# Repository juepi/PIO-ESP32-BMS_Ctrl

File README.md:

# Introduction 
This project is intended to be used as an WiFi/MQTT interface to the [Daly Smart BMS Systems](https://www.aliexpress.com/store/4165007) and Victron VE.Direct devices based on my PlatformIO ESP32 Template.  
Primarily, the code reads status data from the Daly BMS, Victron VE.Direct PV charger and SmartShunt and sends it to your MQTT broker at a configurable interval. It automatically switches the load-SSR on if the batteries are fully charged (2 configurable SOC limits) and off if the batteries are drained (also configureable SOC limit). Load-SSR can also be switched manually by setting the corresponding MQTT topic to `on` or `off`. The primary source for the battery SOC is the **Victron SmartShunt**.  
Last but not least, the firmware also allows you to handle an external active balancer through an additional SSR as recommended by [Andy](https://www.youtube.com/watch?v=yPmwrPOwC3g). However, i have added a second condition beside the 3.4V cell voltage: we're only enabling the active balancer if the voltage difference between the highest and lowest cell is above an configurable threshold (defaults to 30mV, configurable via MQTT topic `t_Ctrl_Cfg_SSR2_CdiffOn`).  
To configure the firmware for your needs, see files `user-config.h` and `mqtt-ota-config.h`, also see [**PlatformIO ESP32 Template**](https://github.com/juepi/PIO-ESP32-Template) readme (WiFi setup etc.).

## Mandatory Hardware Requirements
- 1x [WEMOS S2 Mini](https://www.wemos.cc/en/latest/s2/s2_mini.html) or any other ESP32 should work (adopt `platformio.ini`to your needs)
- 1x [Daly Smart BMS Systems](https://www.aliexpress.com/store/4165007) with UART port
- a Lithium battery fitting your requirements and BMS
- 1x [Victron SmartSolar](https://www.victronenergy.com/solar-charge-controllers/smartsolar-100-30-100-50) charger (or any other charger supporting the text version of the VE.Direct protocol)
- 1x [Victron SmartShunt](https://www.victronenergy.com/battery-monitors/smart-battery-shunt) with the amps required for your setup
- 3x [ADUM1201 UART Isolators](https://www.amazon.de/s?k=adum1201) or any other digital isolators you prefer
- 1x [AQW212EH Optocoupler](https://na.industrial.panasonic.com/products/relays-contactors/semiconductor-relays/lineup/photomos-relays/series/12512/model/12513)
- 1x [Active Balancer](https://aliexpress.com/item/4001176521939.html)
- a local WiFi network with a MQTT broker
- Sunlight. :wink:

## Status
What you are looking at here is the **second major release** of this firmware. If you want to see how it all started or you're interested in the problems I've encountered up to this point, take a look at the [final v1 release readme](https://github.com/juepi/PIO-ESP32-BMS_Ctrl/tree/v1.3.0).  
The hardware part is also finished now, see [KiCad folder](https://github.com/juepi/PIO-ESP32-BMS_Ctrl/tree/main/KiCad).

## Safety Guide
Keep in mind that you are working with potentially dangerous electricity levels depending on the hardware you use. Take any precautions necessary!

## Local Requirements
You need to do the initial battery setup on the Daly BMS using the included Bluetooth adapter and Daly's SmartBMS app, as the used [library](https://github.com/maland16/daly-bms-uart) does not support setting configuration parameters. Victron devices can use the VictronConnect App in parallel to the (read only) serial output on the VE.Direct port.  
An active balancer is highly recommended, as the internal passive balancer of the Daly BMS is useless. [Andy from the Off-Grid Garage](https://www.youtube.com/watch?v=yPmwrPOwC3g) has picked up this topic recently, and i've decided to add the active-balancing control as he suggests it into the firmware. Note that you will need an active balancer that will allow you to start the balancing by shorting 2 pins, like [this one from AliExpress](https://aliexpress.com/item/4001176521939.html). You will need to remove the solder chunk from the pads labeled "Run", this will reveal 2 seperate soldering pads. Solder 2 wires to the pads and connect them to an optocoupler output, in example [AQW212EH](https://na.industrial.panasonic.com/products/relays-contactors/semiconductor-relays/lineup/photomos-relays/series/12512/model/12513).

## An important notice on connecting the ESP32 to your BMS and VE.Direct
Take caution when connecting the ESP to the UART ports: the internal electronics of the BMS (including UART port) use "battery ground", whereas other connected devices (i.e. load, charger) use the "power ground". **NEVER EVER** connect these different grounds or magic smoke will leave your electronics! To avoid this, make sure to isolate **anything** coming from or going into the UART ports of the Daly BMS and your VE.Direct devices. For UART RX/TX, a **ADUM1201** isolator chip works well for me.

## Credits
Thanks to [maland16 and softwarecrash](https://github.com/maland16/daly-bms-uart) for providing a library to interact with the Daly Smart BMS.  
Thanks to [cterwilliger](https://github.com/cterwilliger/VeDirectFrameHandler/tree/master) for his Victron VE.Direct frame handler, which has been integrated into this project since v1.2.0. Note that the source is in the lib directory, not from github, as i needed to include [the buffer overflow patch](https://github.com/cterwilliger/VeDirectFrameHandler/pull/10). I have also added a frameCounter which increments when a valid frame is decoded (to ease handling of fresh data) and a function which looks up array index numbers by Name label (required for SmartShunt!).

# Bugs and Workarounds
- Both data frame arrays of the VeDirectFrameHandler (Charger and SmartShunt) keep increasing over time due to transmission/decoding errors (I assume!) leading to new (non-existing) data labels/values that are added to the arrays. VeDirectFrameHandler maxes out at 40 Labels, so this should not lead to any problems (in terms of buffer overflow), not sure how this is possible however as every frame has a checksum. Due to this problem, also garbage values will be decoded every now and then, so I've added additional validity checks when new data was received (especially SoC).
- VeDirectFrameHandler data from the SmartShunt is "sorted" randomly in the veValue/veName arrays, which breaks the "hardcoded" index numbers I used to get the values from the data arrays. I've fixed this by adding a function to the library that allows you to fetch the arrays index number from a given veName tag. This may also happen with data from the SmartSolar chargers (one out of 2 chargers show this "problem" in my setup).
- OneWire doesn't seem to work on high-numbered GPIO pins (tested with > 36); using IO4 works fine!
- It seems that a high frequency toggling of SSR1 and SSR3 relay may occured at firmware boot - i have not been able to identify the root cause, it only happens when the SSRs automatic-mode is enabled. Done some obviously not so successful improvements over time, but as of **v2.6.1** this error still seems to occur randomly. My latest idea on how to work around this issue was to delay handling of the "auto" SSR settings for 15sec after firmware boot with **v2.7.0**. Time will tell if this helped, first tests look promising.
- An **"offgrid mode"** has been added (**v2.4.3**) as i've experienced that certain battery loads (like my offgrid inverter) causes the OneWire communication to fail. I assume that the inverter causes high noise on the DC wires, but as only OneWire communication is affected, i decided to add this MQTT on/off switchable function to allow skipping OneWire readouts (all sensors will be set to 11°C in offgrid mode, see `t_Ctrl_Cfg_Offgrid_Mode` in `user-config.h`). Plugging in the offgrid inverter is only done in case of a long lasting power outage, which has not happened yet (and hopefully never will), so i can live with that limitation. **A note on failing OneWire communication:** in my case the only way to recover OW-communication was to power down the ESP (remove power from the OW sensors), it seems that the controller inside the sensors hung and rebooting the ESP did not help.
- Although all serial communication to the BMS and Victron devices uses some sort of CRC, it rarely happens that implausible values are reported. To avoid reacting with failsafe actions due to wrong values, several plausibility checks have been added starting with `v2.0.2`.

# Version History

## v2.0.0
- Initial Commit, removed overhead from v1
- Improved handling of SSRs (manual switching through MQTT)

## v2.0.1
- Added condition to enable balancer on large cell voltage diff
- Removed condition to enable balancer on PV power threshold
- removed balancer "minimum ON duration" timer
- cleaned up serial connection state handling
- added more textual output to `CtrlStatTXT` topic; now publishes info on every action the controller takes (like enable/disable load or balancer)

## v2.0.2
- MQTT topic `Daly_dV` now reports mV
- Sending int instead of float  to MQTT topics for Daly temperature and SOC
- Added error detection for VE.Direct data readouts (SOC)
- Added some currently unused pin defines to match KiCad schematics
- Added additional plausibility check for SoC data from SmartShunt

## v2.0.3
- Added optional OneWire support for DS18B20 temperature sensors (enable in `platformio.ini`) - doesn't work yet

## v2.0.4
- Moved OneWire GPIO to IO4, this one works

## v2.1.0
- Fixed missing VeDirectFrameHandler lib (**see Note below!**), which i've trashed somehow as it seems..; now loaded through `platformio.ini`
- Fixed Hostname limitation of ESP32-Template
- Renamed `user_setup.h` to more suitable `user-config.h`

## v2.1.1
- Added SSR3 and SSR4 initialization (default state OFF)
- Fixed high delays due to OneWire `getTempCByIndex()` calls when no sensors are available
- Added Timeout handling for OneWire sensors
- Improved VE.Direct data error and connection handling
- Bugfix for WiFi hostname setup (compile error for v2.1.0 when using hostname with dash)
- Added SSR3 for manual switching through MQTT
- Added safety shutdown of loads when communication to Daly BMS or Victron SmartShunt runs into timeout

## v2.2.0
- Reworked Load and Balancer SSR handling (now fully configurable through MQTT topics)
- Updated MQTT subscription handling (PIO-ESP32-Template v1.1.0)
- OTA Updates are now mandatory
- Removed MQTT control of Daly BMS FETs (they are a safety feature, you shouldn't mess with them manually)
- Added additional safety features (Balancer alarm mode for high cellDiff, load shutdown for minimum battery voltage)

## v2.2.1
- Re-added periodic publishing of SSR states (basically for plots in FHEM)
- Bugfix on SSR state handling at firmware boot

## v2.3.0
- Added ability to run without WiFi / MQTT broker connection (based on [**PIO-ESP32-Template v1.2.0**](https://github.com/juepi/PIO-ESP32-Template))

## v2.3.1
- Removed unneccesary SSR handling at firmware boot (just let auto-mode do the magic)
- Setting all SSR state topics to "OFF" on the broker at startup to match the actual firmware boot state 
- High frequency toggling of SSR3 state at firmware boot hopefully fixed

## v2.4.0
- Added error/recovery handling for over-temperature situations (OW-sensors and Daly BMS sensor)
- Improved under-voltage and communication error/recovery handling
- Removed Balancer Alarm mode, as balancing an empty battery does not make sense
- Added additional safety check to turn off loads at high cell diff voltage (stopping discharge should probably not further increase cell diff)
- Added verification of Daly celldiff readout (reports implausible high changes between 2 readouts in rare occurences)

## v2.4.1
- Minor status output changes (investigating readout error loop on SmartShunt)
- Added ESP reboot when reaching configurable threshold of subsequent SmartShunt read failures (defaults to 60 -> 1 minute)

## v2.4.2
- No longer send Controller status text messages retained
- Added global controller Alarm flag being published via MQTT; if a safety function triggers a critical condition, the flag switches to "on" (see topic `t_Ctrl_Alarm` in `user-config.h`)
- "Bugfix" in SmartShunt SOC verification ("error loop" from v2.4.1 - basically `VSS_MAX_SOC_DIFF` was set too low to 0.5% instead of 5%)

## v2.4.3
- Added status text message when not discarding unrealistic high Daly BMS voltage diff
- Increased max number of unrealistic subsequent voltage diff values from Daly BMS which will be discarded (from 2 to 4)
- Switched balancer power-off condition from single cell to all cells below `SSR2.CVOff` (previous conditions could lead to Auto-mode rapidly toggling balancer if a single cell is above enable and another one is below disable voltage)
- Added "offgrid mode", can be enabled when "noisy" battery loads break OneWire communication (in example, when connecting an offgrid inverter)

## v2.4.4
- Allow larger SOC changes when charger switches to absorption mode (battery full -> SmartShunt corrects SOC to 100%)

## v2.5.0
- Functionality cleanups
    - Removed Low-PPV threshold (everything below High-PPV threshold is considered as low now)
    - Removed Low/High-PPV Off-SOC for SSRs (simply useless - switched to a single Off-SOC)
- Removed ESP reboot for SmartShunt read failures (useless)

## v2.5.1
- Use Victron SmartShunt voltage (instead of Daly data) as battery pack voltage source for safety checks
- recover previous SSR Auto-mode settings instead of enabling all auto modes when recovering from critical states

## v2.6.0
- Added support for optional 2nd SmartSolar charger (VE.Direct, using GPIO39 for RX; enable in `platformio.ini`)
- Upgraded to latest `EspSoftwareSerial` library version
- Added plausibility check for SmartShunt pack voltage (discard value if difference to previous readout is more than `VSS_MAX_V_DIFF` defined in `user-config.h`)

## v2.6.1
- Immediately publish Controller-Alarm flag via MQTT when alarm occurs (or recovers)
- Fixed error in cell temperature alarm handling

## v2.7.0
- Added web interface (network status checking / reboot ESP)
- Upgraded underlying [**PIO-ESP32-Template to v1.4.0**](https://github.com/juepi/PIO-ESP32-Template)
- Checking validity of most important Victron SmartShunt data 10sec after firmare startup (ESP will reboot if no valid SOC or voltage is available)
- Automatic SSR-handling is started 15sec after ESP boot if enabled (hopefully solves fast-toggling SSR issue)
- Publishing of data to MQTT will start after `DATA_UPDATE_INTERVAL` to avoid publishing wrong/incomplete data directly at firmware boot

## v2.7.1
- Added Moving Average class to calculate short (1 min) and long (1hr) averages for Victron chargers PPV values
- Added validation of OneWire temperature readouts (reject reading if diff between subsequent readouts is higher than `OW_MAX_TEMP_DIFF`)
- Updated DallasTemperature library to [version 4.0.5](https://registry.platformio.org/libraries/milesburton/DallasTemperature)

# NOTE on missing VeDirectFrameHandler library

I somehow managed to not to include the VeDirectFrameHandler library into previous commits as it was intended. **This affects all versions prior v2.1.0!**  
If you want to build an older release, you can easily fix this by adding my [fork of VeDirectFrameHandler](https://github.com/juepi/VeDirectFrameHandler) into the library section of `platformio.ini`:

```
lib_deps =
    https://github.com/juepi/VeDirectFrameHandler
    ...
```

Have fun,  
Juergen

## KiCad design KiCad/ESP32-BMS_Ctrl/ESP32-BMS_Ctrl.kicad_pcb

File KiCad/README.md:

# KiCad Project Files
The hardware part of the BMS-Controller constists of 2 boards, where the small and simple DE-9 Adaptor board is meant to be placed in your battery box. It will only concentrate all required wires on a 9pin D-Sub connector, allowing you to use a common (straight) serial cable to connect to the actual BMS-Controller board with the ESP32 (which is located outside of the metal battery box in my case).  
Schematics should be straight forward and documented. Don't forget to add isolators into the wires to/from VE.Direct devices and your Daly BMS (i have soldered them directly into the wires, so they are not on the PCBs). Both PCBs only use THT parts (no SMT).

## Optional Features
I have added a second AQW212EH opto-coupler as well as 2 additional dual P-channel MOSFET driven power outputs. This hardware is optional. Depending on your load currents, you may install the paralleled MOSFETs (Q4-Q6) or not. I have done load tests with 2 paralleled MOSFETs with up to 15A without any problems. Do note that you will probably have to install more powerful MOSFETs with lower RDSon than the one mentioned in the schematics for such high currents. I have tested with 2 [IXYS IXTP140P05T](https://www.littelfuse.com/media?resourcetype=datasheets&itemid=309f84bc-aa60-4d40-b2f9-2c59ecb0b7b8&filename=littelfuse-discrete-mosfets-p-channel-ixt-140p05t-datasheet). Additionally, you may want to screw at least small heat sinks to the FETs at this current levels.  
Additionally, i have prepared a pin header connector on the DE-9 adaptor board which will let you connect up to 5 [DS18B20](https://www.analog.com/media/en/technical-documentation/data-sheets/ds18b20.pdf) OneWire temperature sensors in parasitic mode.  
J4 and J5 can be used if you have an "external use" for the OptoMOS outputs of U2. Be sure not to place any other components on the OptoMOS output if you want to use the "external connector" (for J4 -> do not populate R2, R6 and R7, and of course Q2 and Q5) to keep them potential free.

## Production Files
Gerber files are prepared for PCB manufacturing at [jlcpcb.com](https://jlcpcb.com). If you are expecting higher currents on the power outputs, you may want to double up the **copper weight to 2oz** for the BMS-Controller PCB on your order.

# Version History

## v1.1
- Initial commit with some improvements to allow more current on BMS-Controller board (SSR1, SSR3 and SSR4)

## v1.2
- Replaced B2B-XH connector footprints with version w/o guidance hole
- maximized spacing between 2 paralleled MOSFETs to allow mounting a TO-220 heat sink
- Fixed too narrow GND connections for screw terminals; updated Gerber data
- Added silkscreen text to explain installation direction of ESP module

## v1.3
- Re-routed OneWire pin to GPIO4 (tested ok with 2 sensors)

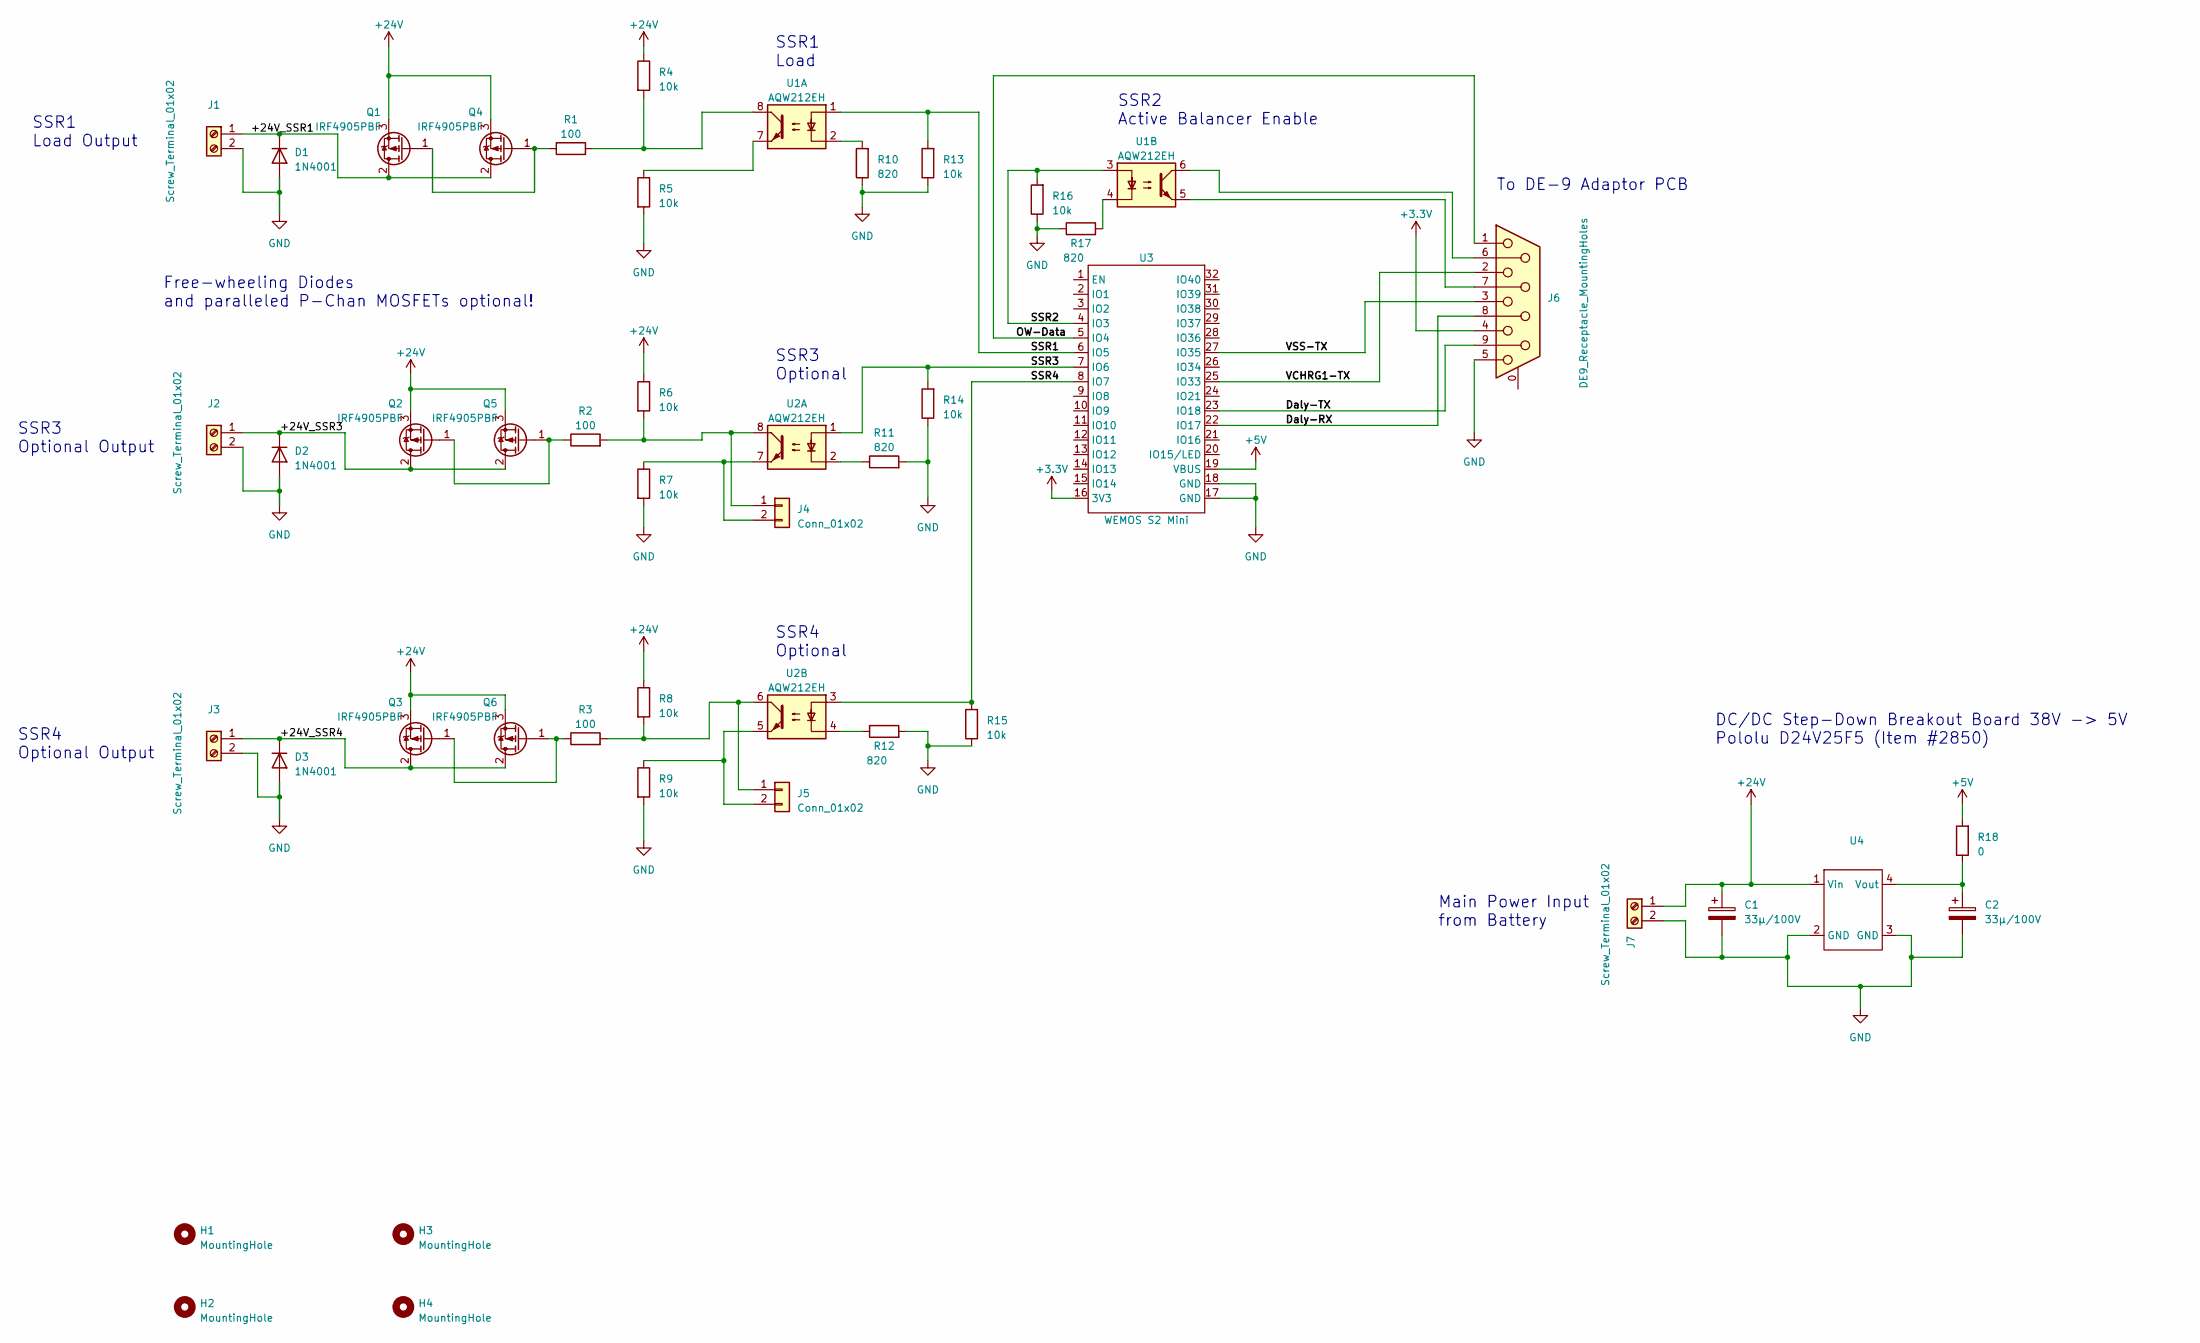
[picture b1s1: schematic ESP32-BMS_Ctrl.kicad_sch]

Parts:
C1, C2: 33µ/100V; CP_Radial_D10.0mm_P5.00mm
D1, D2, D3: 1N4001; D_DO-41_SOD81_P10.16mm_Horizontal
H1, H2, H3, H4: MountingHole; MountingHole_3.2mm_M3
J1, J2, J3, J7: Screw_Terminal_01x02; TerminalBlock_1x02_P5.00mm_Horizontal
J4, J5: Conn_01x02; JST_XH_B2B-XH-A_1x02_P2.50mm_Vertical
J6: DE9_Receptacle_MountingHoles; DSUB-9_Female_Horizontal_P2.77x2.84mm_EdgePinOffset9.90mm_H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
Q1, Q2, Q3, Q4, Q5, Q6: IRF4905PBF; TO-220-3_Vertical
R1, R2, R3: 100; R_Axial_DIN0207_L6.3mm_D2.5mm_P10.16mm_Horizontal
R4, R5, R6, R7, R8, R9, R13, R14, R15, R16: 10k; R_Axial_DIN0207_L6.3mm_D2.5mm_P10.16mm_Horizontal
R10, R11, R12, R17: 820; R_Axial_DIN0207_L6.3mm_D2.5mm_P10.16mm_Horizontal
R18: 0; R_Axial_DIN0207_L6.3mm_D2.5mm_P10.16mm_Horizontal
U1, U2: AQW212EH; DIP-8_W7.62mm_Socket
U3: WEMOS S2 Mini; WEMOS_S2_Mini
U4: Pololu_D24V25F5

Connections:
+3.3V: J6.4, U3.16 (3V3)
+5V: R18.2, U3.19 (VBUS)
+24V: C1.1, J7.1, Q1.3 (S), Q2.3 (S), Q3.3 (S), Q4.3 (S), Q5.3 (S), Q6.3 (S), R4.1, R6.1, R8.1, U4.1 (Vin)
/+24V_SSR1: D1.1 (K), J1.1, Q1.2 (D), Q4.2 (D)
/+24V_SSR3: D2.1 (K), J2.1, Q2.2 (D), Q5.2 (D)
/+24V_SSR4: D3.1 (K), J3.1, Q3.2 (D), Q6.2 (D)
/Daly-RX: J6.8, U3.22 (IO17)
/Daly-TX: J6.9, U3.23 (IO18)
/OW-Data: J6.1, U3.5 (IO4)
/SSR1: R13.2, U1.1, U3.6 (IO5)
/SSR2: R16.2, U1.3, U3.4 (IO3)
/SSR3: R14.2, U2.1, U3.7 (IO6)
/SSR4: R15.2, U2.3, U3.8 (IO7)
/VCHRG1-TX: J6.2, U3.25 (IO33)
/VSS-TX: J6.3, U3.27 (IO35)
GND: C1.2, C2.2, D1.2 (A), D2.2 (A), D3.2 (A), J1.2, J2.2, J3.2, J6.5, J7.2, R5.2, R7.2, R9.2, R10.1, R11.2, R12.2, R13.1, R14.1, R15.1, R16.1, R17.1, U3.17 (GND), U3.18 (GND), U4.2 (GND), U4.3 (GND)
unnamed: J4.1, R2.2, R6.2, U2.8
unnamed: J4.2, R7.1, U2.7
unnamed: J5.1, R3.2, R8.2, U2.6
unnamed: J5.2, R9.1, U2.5
unnamed: J6.6, U1.6
unnamed: J6.7, U1.5
unnamed: Q1.1 (G), Q4.1 (G), R1.1
unnamed: Q2.1 (G), Q5.1 (G), R2.1
unnamed: Q3.1 (G), Q6.1 (G), R3.1
unnamed: R1.2, R4.2, U1.8
unnamed: R5.1, U1.7
unnamed: R10.2, U1.2
unnamed: R11.1, U2.2
unnamed: R12.1, U2.4
unnamed: R17.2, U1.4
unnamed: C2.1, R18.1, U4.4 (Vout)

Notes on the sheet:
To DE-9 Adaptor PCB
Main Power Input from Battery
SSR4 Optional Output
Free-wheeling Diodes and paralleled P-Chan MOSFETs optional!
SSR2 Active Balancer Enable
SSR4 Optional
SSR3 Optional
DC/DC Step-Down Breakout Board 38V -> 5V Pololu D24V25F5 (Item #2850)
SSR1 Load
SSR1 Load Output
SSR3 Optional Output

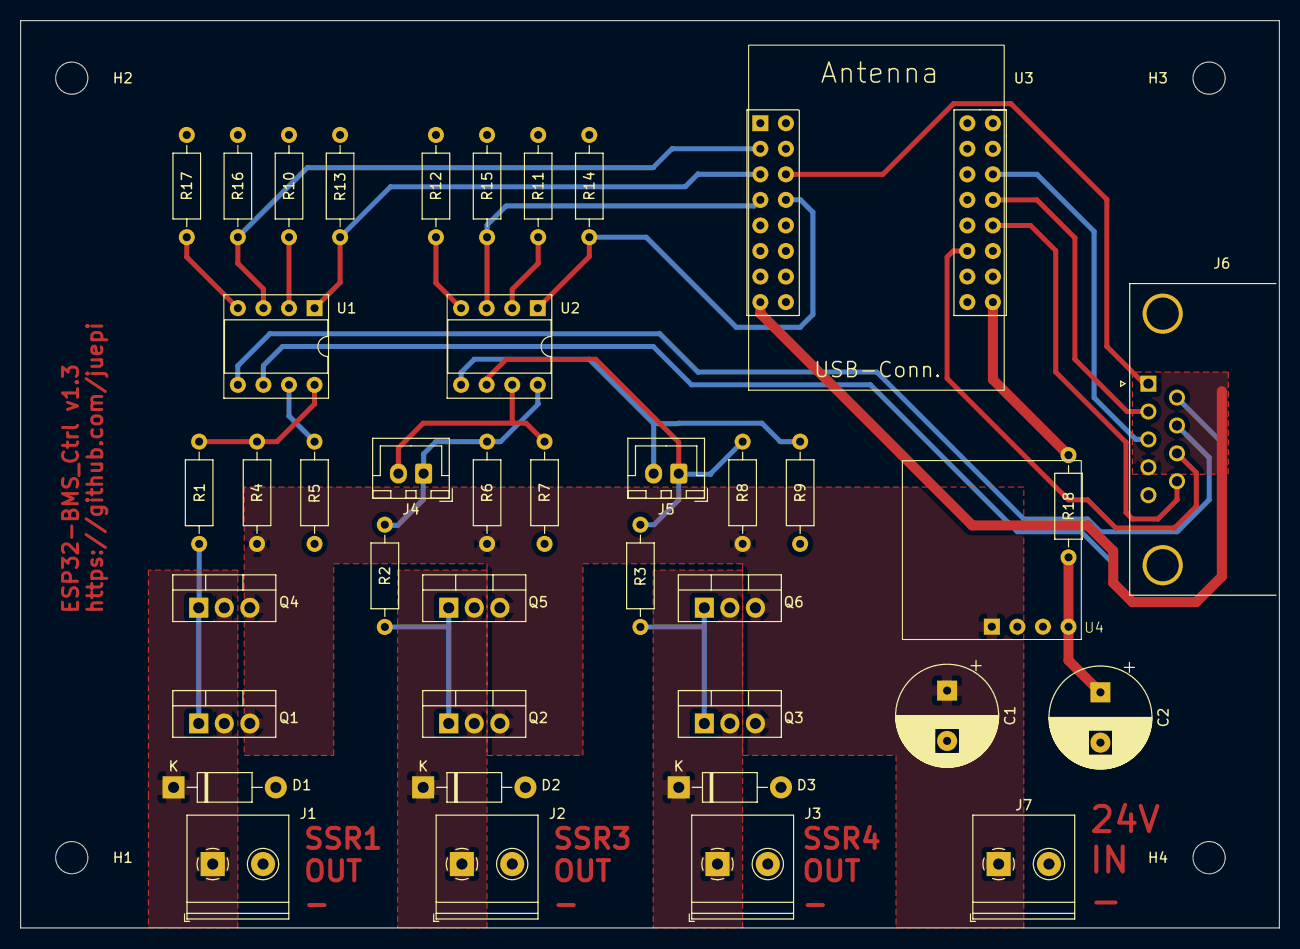
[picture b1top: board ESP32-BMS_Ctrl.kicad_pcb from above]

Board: 2 copper layers, 125.1 x 90.2 mm, 44 parts (0 on the bottom side), 32 nets.

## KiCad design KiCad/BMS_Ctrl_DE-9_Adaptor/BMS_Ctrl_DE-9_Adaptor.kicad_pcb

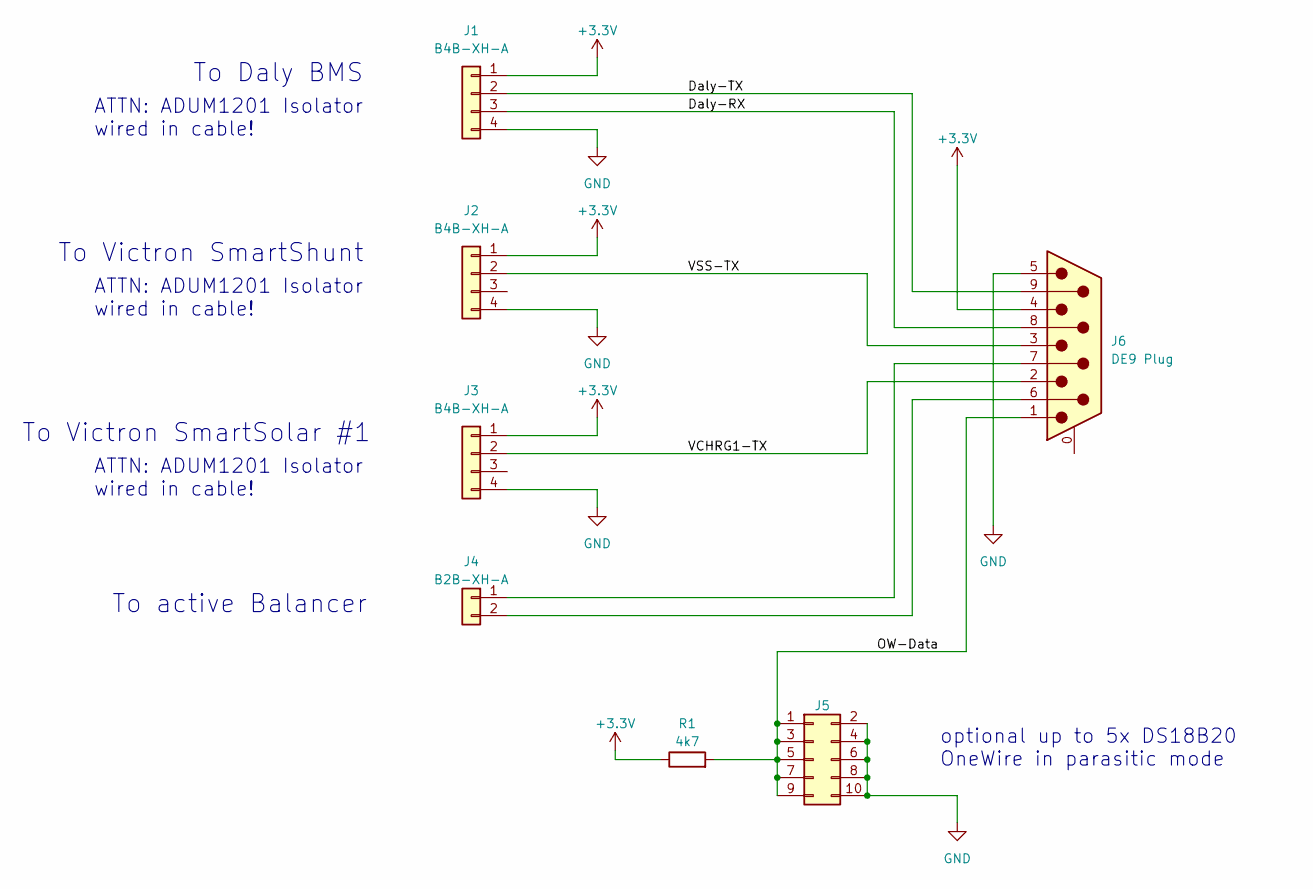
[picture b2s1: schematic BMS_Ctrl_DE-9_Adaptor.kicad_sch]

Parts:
J1, J2, J3: B4B-XH-A; JST_XH_B4B-XH-A_1x04_P2.50mm_Vertical; Manufacturer_Part_Number B4B-XH-A(LF)(SN)
J4: B2B-XH-A; JST_XH_B2B-XH-A_1x02_P2.50mm_Vertical; Manufacturer_PN B2B-XH-A(LF)(SN)
J5: Conn_02x05_Counter_Clockwise; PinHeader_2x05_P2.54mm_Vertical
J6: DE9 Plug; DSUB-9_Male_Horizontal_P2.77x2.84mm_EdgePinOffset9.90mm_Hou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
R1: 4k7; R_Axial_DIN0207_L6.3mm_D2.5mm_P10.16mm_Horizontal

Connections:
+3.3V: J1.1, J2.1, J3.1, J6.4, R1.1
/Daly-RX: J1.3, J6.8
/Daly-TX: J1.2, J6.9
/OW-Data: J5.1, J5.3, J5.5, J5.7, J5.9, J6.1, R1.2
/VCHRG1-TX: J3.2, J6.2
/VSS-TX: J2.2, J6.3
GND: J1.4, J2.4, J3.4, J5.2, J5.4, J5.6, J5.8, J5.10, J6.5
unnamed: J4.1, J6.7
unnamed: J4.2, J6.6

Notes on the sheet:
To Victron SmartSolar #1
ATTN: ADUM1201 Isolator wired in cable!
To Daly BMS
To active Balancer
To Victron SmartShunt
optional up to 5x DS18B20 OneWire in parasitic mode

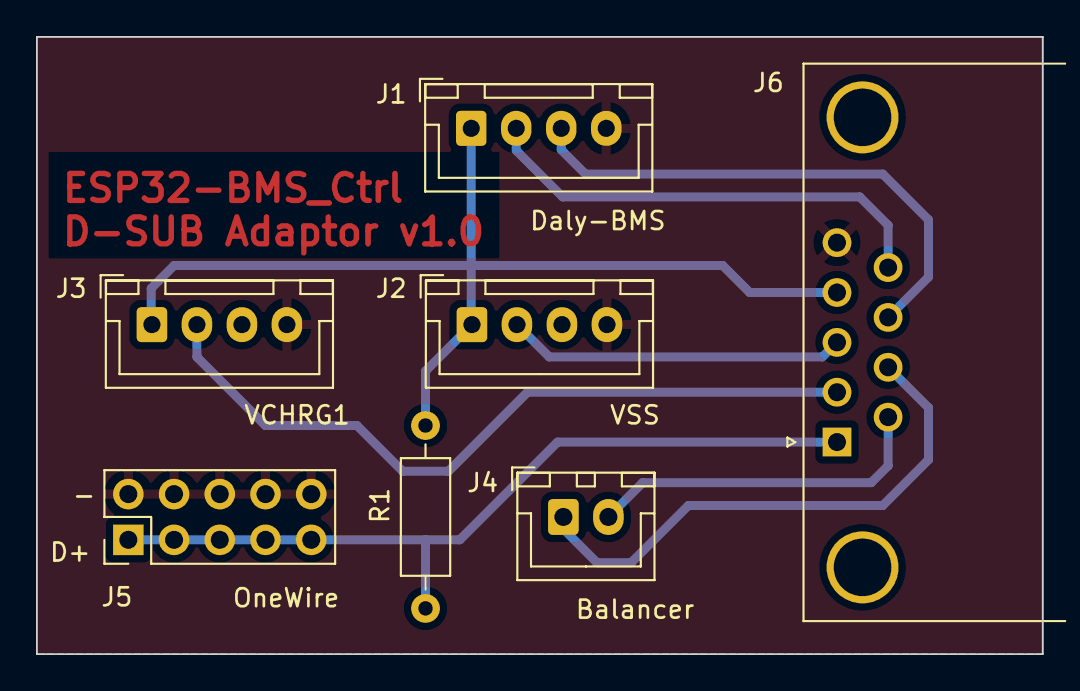
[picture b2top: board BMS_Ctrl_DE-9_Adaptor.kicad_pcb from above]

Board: 2 copper layers, 55.9 x 34.3 mm, 7 parts (0 on the bottom side), 9 nets.

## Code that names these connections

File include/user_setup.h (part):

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// User SSR
// HIGH level -> SSR is switched ON
//
#define SSR1 5 // Battery Load Switch
#define SSR2 3 // Active Balancer Enable
#define SSR3 6 // unused - defined to match KiCad board
#define SSR4 7 // unused - defined to match KiCad board

//
// OneWire Bus
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//
// Load settings (SSR1)
//
#define ENABLE_LOAD_SOC 80     // SOC at which to enable the load (SSR1)
#define DISABLE_LOAD_SOC 10    // SOC at which load will be disconnected
#define HIGH_PV_AVG_PWR 20     // If the average charging power is higher than this..
#define HIGH_PV_EN_LOAD_SOC 50 //.. enable the load at an earlier SOC to avoid wasting PV energy
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#define t_D_CSTAT TOPTREE "Daly_CSTAT"        // Daly Serial connection status
#define t_Ctrl_StatT TOPTREE "CtrlStatTXT"    // ESP Controller status text provided through MQTT (basically to check if UART to Daly BMS is OK)
#define t_Ctrl_StatU TOPTREE "CtrlStatUpt"    // ESP Controller uptime provided through MQTT
#define t_Ctrl_actSSR1 TOPTREE "Ctrl_actSSR1" // Actual state of SSR1 GPIO (on/off)
#define t_Ctrl_actSSR2 TOPTREE "Ctrl_actSSR2" // Actual state of SSR2 GPIO (on/off)
// Subscriptions
#define t_Ctrl_CSw TOPTREE "Ctrl_CSw"   // User-desired state of Daly charging MOSFETs (on/off or dnc for "do not change")
#define t_Ctrl_LSw TOPTREE "Ctrl_LSw"   // User-desired state of Daly discharging MOSFETs (on/off or dnc)
#define t_Ctrl_SSR1 TOPTREE "Ctrl_SSR1" // User-desired state of SSR1 GPIO (on/off/dnc)
#define t_Ctrl_SSR2 TOPTREE "Ctrl_SSR2" // User-desired state of SSR2 GPIO (on/off/dnc)

//
// Data structures
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
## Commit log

2022-09-11 blindly added Daly BMS library
2022-09-18 update readme and version
2022-09-18 update readme formatting
2022-10-09 Daly communcation works, INA226 not
2022-10-09 communication working
2022-10-10 minor updates, readme
2022-10-10 minor updates
2022-10-12 v0.4, see readme
2022-10-15 readme update; crash fixed
2022-11-22 Release 1.0.0
2022-12-15 v1.1.0
2023-01-01 v1.1.1
2023-01-01 reset platformio.ini to wired flash
2023-02-06 v1.20 - added VE.Direct decoding
2023-02-10 v1.2.1 - undone some disimprovements
2023-03-04 Final v1 release v1.3.0 - see README
2023-03-05 initial v2.0.0 release
2023-03-05 readme fix
2023-03-16 Release v2.0.1
2023-03-23 Added KiCad files; Firmware version 2.0.2
2023-03-23 update readmes
2023-03-24 comments / readme updates
2023-03-31 Updated Main PCB to v1.2
2023-04-04 minor updates on main PCB
2023-04-05 update gitignore
2023-04-08 added OneWire support (WIP)
2023-04-09 OneWire working now; updated KiCad data
2023-04-14 v2.10; fixed missing VeDirectFH lib
2023-04-27 v2.1.1; changes see README
2023-05-16 v2.2.0: Major updates, see readme
2023-06-05 minor updates; v2.2.1
2023-06-07 v2.3.0; added "offline mode"
2023-06-08 v2.3.1 - mainly bugfix release
2023-06-12 v2.4.0; major safety features added
2023-06-23 minor updates, see readme
2023-06-23 more minor updates; see readme v2.4.2
2023-06-26 minor improvements and fixes - v2.4.2
2023-07-17 v2.4.3 - see readme
2023-07-30 v2.4.3 - minor updates and workarounds
2023-07-31 readme/comment updates
2023-09-02 minor bugfix
2023-09-03 minor functionality cleanup
2023-09-23 Updated READMEs; replaced dead links
2023-09-23 fixed another dead link
2023-12-07 v2.5.1; minor improvements
2024-08-01 v2.6.0
2025-03-15 v2.6.1 minor bugfixes
2025-03-15 readme corrected
2025-06-03 added webservice; updated to template v1.4.0
2025-06-03 bugfixes and config updates
2025-06-04 F/W startup improvements
2025-06-10 bugfix SS2 H20 Index detection
2025-11-22 v2.7.1; library updates and minor improvements
